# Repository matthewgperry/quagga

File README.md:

# Quagga

## What is Quagga?

Quagga is a custom built split ergonomic diode-less reversible pcb keyboard design.

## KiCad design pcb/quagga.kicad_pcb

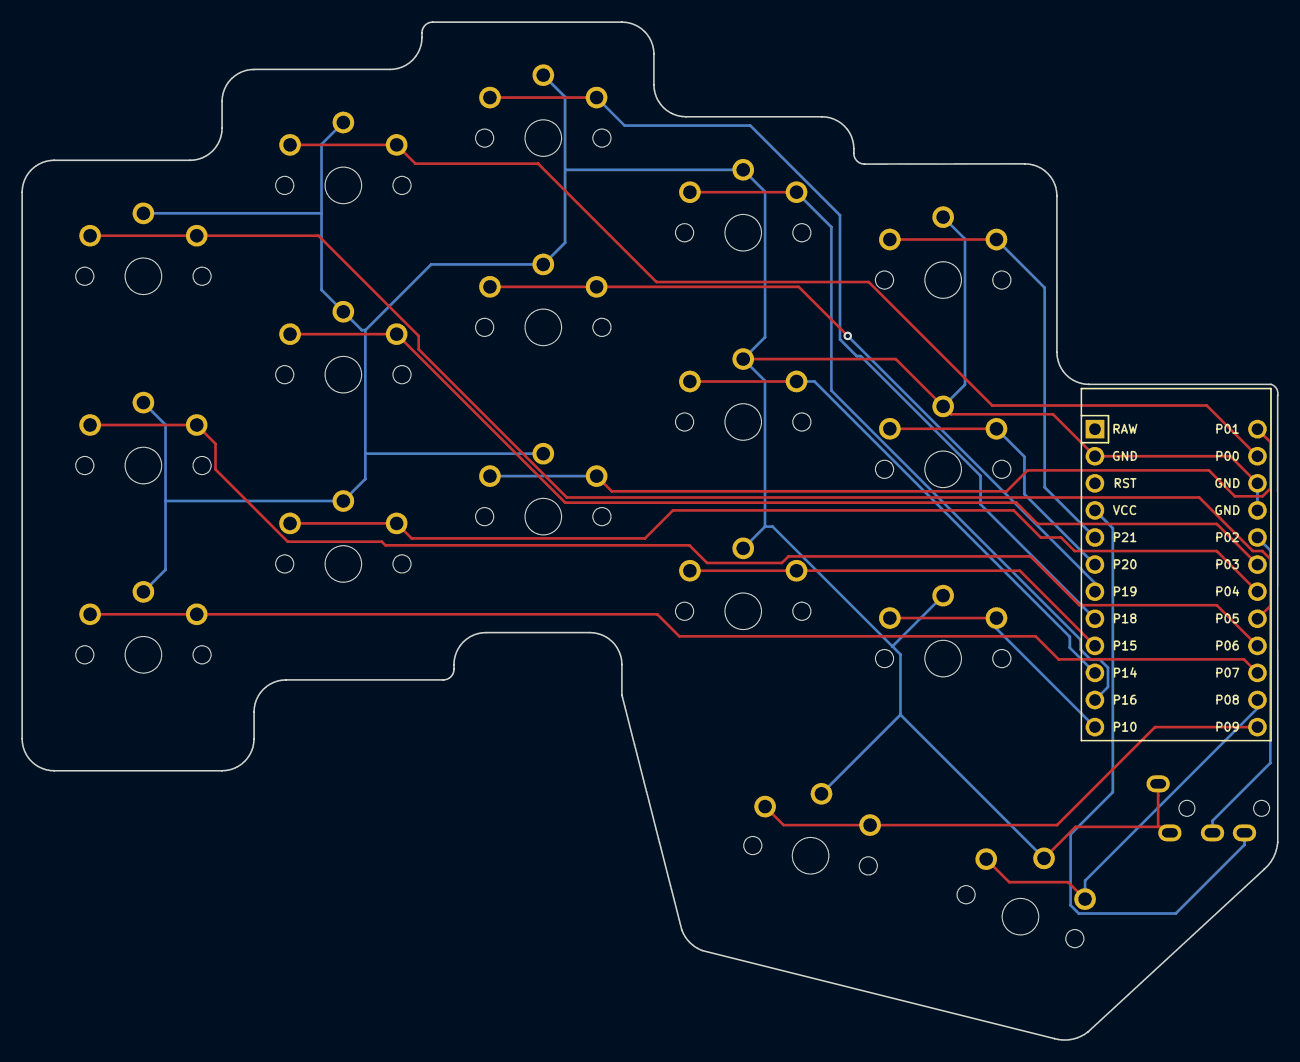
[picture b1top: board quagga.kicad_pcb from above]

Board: 2 copper layers, 117.8 x 95.5 mm, 18 parts (0 on the bottom side), 18 nets.

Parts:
MCU1: ProMicro
S1, S2, S3, S4, S5, S6, S7, S8, S9, S10, S11, S12, S13, S14, S15, S16, S17: PG1350

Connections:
GND: MCU1.2, MCU1.15, MCU1.16, S1.2, S2.2, S3.2, S4.2, S5.2, S6.2, S7.2, S8.2, S9.2, S10.2, S11.2, S12.2, S13.2, S14.2, S15.2, S16.2, S17.2
P0: MCU1.14, S6.1
P1: MCU1.13, S7.1
P3: MCU1.18, S5.1
P4: MCU1.19, S4.1
P5: MCU1.20, S3.1
P6: MCU1.21, S2.1
P7: MCU1.22, S1.1
P8: MCU1.23, S16.1
P9: MCU1.24, S17.1
P10: MCU1.12, S13.1
P14: MCU1.10, S11.1
P15: MCU1.9, S10.1
P16: MCU1.11, S12.1
P18: MCU1.8, S9.1
P19: MCU1.7, S8.1
P20: MCU1.6, S14.1
P21: MCU1.5, S15.1

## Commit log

2022-02-08 Added all files
2022-02-08 Fixed image
